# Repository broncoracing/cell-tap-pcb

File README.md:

# Bronco Racing Segment Monitor PCB

This repository contains the hardware design, firmware, and software calibration scripts for the segment monitor PCB.

The segment monitor contains an STM32f103R8T6 microcontroller which interfaces 15 ADCs (12 external for monitoring cell temperatures and 3 onboard on the PCB.)
A separate break-away board for digital and power isolation is also included.

## Hardware details

The thermistor measurement circuit consists of a 10k thermistor (or connector for a thermistor), a precision 10k reference resistor, and a filter capacitor (The filter capacitor is mostly important to prevent measurement errors due to the changing input impedance of the microcontroller's analog pins when they sample the voltage, this is likely a very small effect that wouldn't cause large errors anyway).

The reference resistor and thermistor form a voltage divider circuit, which allows the resistance of the thermistor to be determined by reading the center voltage.

The circuit is designed specifically to work with 10k NTC thermistors, but it would likely work with any thermistor with a resistance in the 1k-100k range.

Each external thermistor connector also has an LED located next to the connector. This LED indicates whether the thermistor's resistance is valid. If the thermistor is within a reasonable range, the LED will be off. If the microcontroller detects too high or low of a voltage (indicating a short circuit or disconnected thermistor) the LED is turned on. Upon powering up the LEDs will all turn on and off in sequence to verify that the LEDs themselves function correctly.

On the back side of the board (opposite the microcontroller) each cell tap connection connects to an SMD fuse and a trace which leads to the cell tap connector. These fuses are located close to the cell tap connection to meet FSAE rules for fusing of tractive system wires, and eliminate the need for inline fuses on each cell tap wire. 
Due to a minor design oversight, the fuses on the endmost cell taps can be damaged or knocked off the board if the busbars for the Radlok maintenance plugs are rotated too far inwards when the segment is being assembled. Take care when assembling or disassembling the segments to avoid this issue.

## Firmware documentation
The firmware reads data from all the connected thermistors and sends them over the CAN bus at 100ms intervals.

To avoid overloading CAN bus with too many concurrent messages, each segment sends out only 4 thermistor values in each message, and rotates which thermistor temperatures are sent out in each message.

The segment PCB firmware also includes a thermistor calibration routine, which stores measured ADC values for three different temperatures  the Steinhart-Hart equation as described below in the Performance Testing & Analysis section. To perform this calibration, a simple CAN protocol similar to the one utilized by the CAN bootloader was developed. This protocol consists of four commands to perform the following actions:
- Clear calibration data
- Record resistances at a given temperature
- Calculate Steinhart-Hart parameters based on three temperature values
- Read out calibration data over CAN bus and print it to the console

In order to simplify the user experience, a Python command line application was developed to execute these commands and interpret the response sent back over the CAN bus.
This script is located at `firmware/scripts/calibrate.py`. Since I was too lazy to make it automatically detect the CAN bus interface, you'll have to manually set it in the script (or upgrade the script to use a command line parameter), it will be something like `/dev/ttyACM*` on linux.

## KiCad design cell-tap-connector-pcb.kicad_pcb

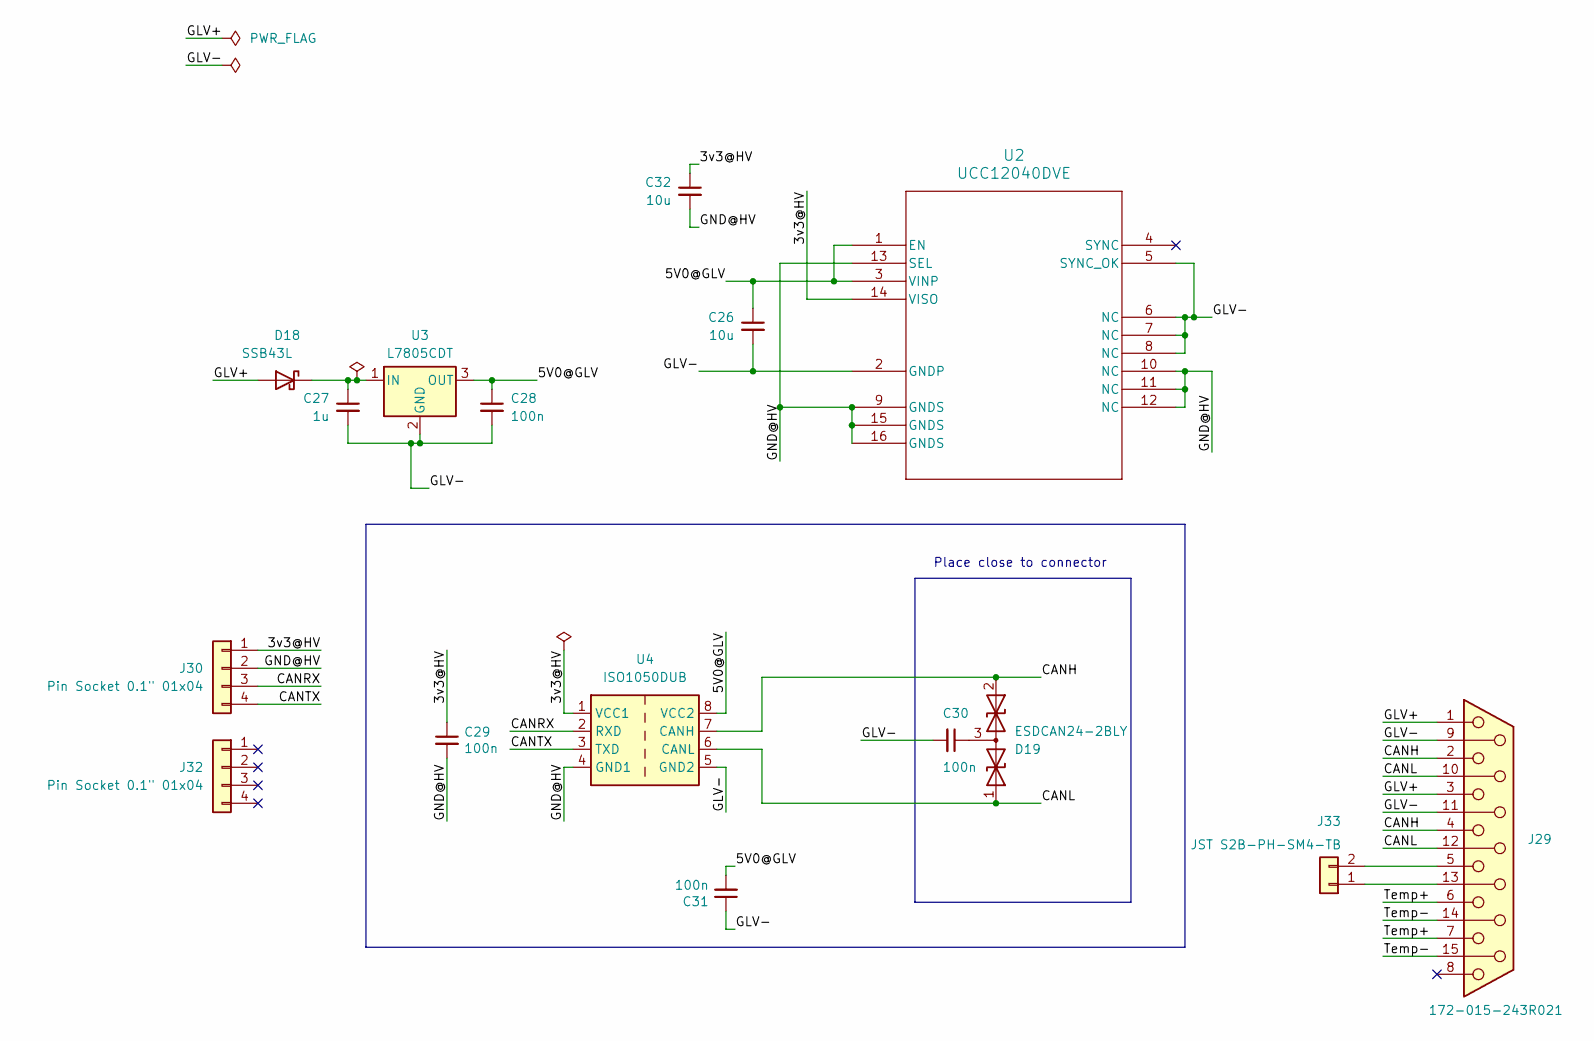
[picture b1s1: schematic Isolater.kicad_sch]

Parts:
C26, C32: 10u; C_0603_1608Metric
C27: 1u; C_0603_1608Metric
C28: 100n; C_0603_1608Metric
C29, C30, C31: 100n; C_0603_1608Metric; LCSC C307331
D18: SSB43L; D_SMA-SMB_Universal_Handsoldering
D19: ESDCAN24-2BLY; SOT-323_SC-70; LCSC C151237
J29: 172-015-243R021; DSUB-15_Socket_Vertical_P2.77x2.84mm
J30, J32: Pin Socket 0.1" 01x04; PinSocket_1x04_P2.54mm_Vertical
J33: JST S2B-PH-SM4-TB; JST_PH_S2B-PH-SM4-TB_1x02-1MP_P2.00mm_Horizontal
U2: UCC12040DVE; SO_0DVER_TEX
U3: L7805CDT; TO-252-2
U4: ISO1050DUB; SOP-8_6.62x9.15mm_P2.54mm

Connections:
/Isolator/3v3@HV: C29.1, C32.1, J30.1, U2.14 (VISO), U4.1 (VCC1)
/Isolator/5V0@GLV: C26.1, C28.1, C31.2, U2.1 (EN), U2.3 (VINP), U3.3 (OUT), U4.8 (VCC2)
/Isolator/CANH: D19.2 (A2), J29.2, J29.4, U4.7 (CANH)
/Isolator/CANL: D19.1 (A1), J29.10, J29.12, U4.6 (CANL)
/Isolator/CANRX: J30.3, U4.2 (RXD)
/Isolator/CANTX: J30.4, U4.3 (TXD)
/Isolator/GLV+: D18.2 (A), J29.1, J29.3
/Isolator/GLV-: C26.2, C27.2, C28.2, C30.2, C31.1, J29.9, J29.11 (P111), U2.2 (GNDP), U2.5 (SYNC_OK), U2.6 (NC), U2.7 (NC), U2.8 (NC), U3.2 (GND), U4.5 (GND2)
/Isolator/GND@HV: C29.2, C32.2, J30.2, U2.9 (GNDS), U2.10 (NC), U2.11 (NC), U2.12 (NC), U2.13 (SEL), U2.15 (GNDS), U2.16 (GNDS), U4.4 (GND1)
/Isolator/Temp+: J29.6, J29.7
/Isolator/Temp-: J29.14, J29.15
unnamed: C27.1, D18.1 (K), U3.1 (IN)
unnamed: C30.1, D19.3 (common)
unnamed: J29.13, J33.1
unnamed: J29.5, J33.2

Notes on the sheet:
Place close to connector

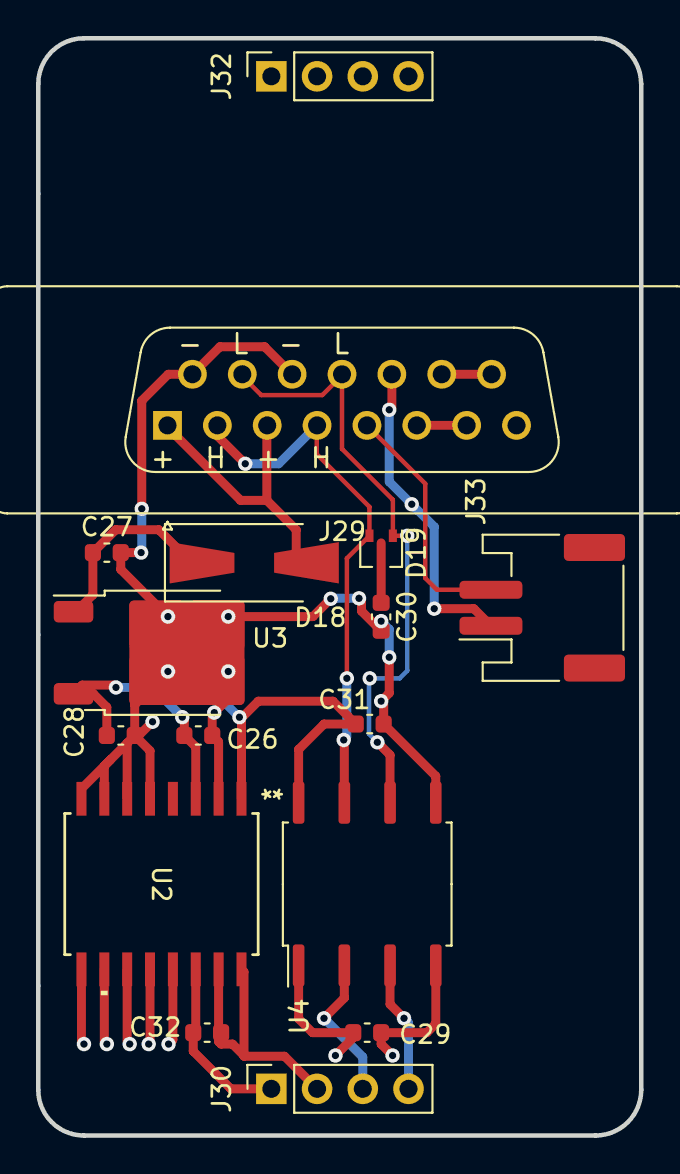
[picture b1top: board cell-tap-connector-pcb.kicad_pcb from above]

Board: 4 copper layers, 33.5 x 61.0 mm, 16 parts (0 on the bottom side), 15 nets.

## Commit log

2023-10-04 initial layout
2023-10-05 more layout and memes
2023-10-23 removed slots
2023-10-23 Update kibot.yml again
2023-11-12 Update kibot.yml (hopefully for the last time)
2023-11-12 Update kibot.yml (#1)
    Update kibot.yml
2023-11-12 Update kibot.yml to kicad 7
2023-11-12 remove net class labels, which are unsupported by kibot :(
2023-11-12 hopefully appease drc checker
2023-11-13 fix drc/erc errors
2023-12-07 Created test firmware
2024-03-04 added calibration and bootloader support
2024-04-09 update firmware to do calibration and work with orion BMS
2024-04-20 Add README
2025-06-30 add big/little endian swap for board 0 bms data
2025-11-29 Kicad Update
2025-12-01 PCB Update
